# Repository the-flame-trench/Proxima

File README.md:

# Proxima
Repo for the open source Proxima AstroCamera family

## About
The Proxima AstroCamera is a general purpose CCD/CMOS imager intended for use for amateur astrophotography and citizen science/outreach.  The project aligns closely with [The Flame Trench](http://theflametrench.com)'s [Gaze](http://theflametrench.com/flagship#/gaze) robotic observatory project.  The intent is to develop configurable CCD/CMOS front-end variants and an ASCOM compatible, FPGA-based back-end compute module.  This will come in ethernet based Alpaca and USB-3 based ASCOM/native variants.

## Specifications
The following are provisional design goals of the Proxima project:
* DSLR CCD/CMOS
   * mono/bayered
   * interline/full frame
* Programmable bias voltages, to allow for the front-end to be CCD agnostic
* Tuned clocking drivers for the same reason
* Separate CMOS driver front-end variant
* Full ASCOM compliancy, for compatibility with current astrophotography/astronomy session management and capture software suites
* Active cooling, to reduce dark current noise to the minimum feasible
* USB 3 support, to prevent data downlinking causing a bottleneck within the system, and allowing for fast image frequencies
* Ethernet support in a Linux SoC/Alpaca back-end variant
* Memory buffers for fast framerate CMOS readout
* Sealed/purged cold room
   * Provisional goal which would allow for much colder CCD temperatures by absorbing or purging moisture from the enclosure
* 12-19V DC supply, to allow for AC mains + power supply or power direct from battery

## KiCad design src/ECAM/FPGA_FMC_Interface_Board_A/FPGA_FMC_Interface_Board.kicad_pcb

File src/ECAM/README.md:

# Proxima ECAM
This folder contains the electronic hardware source for the Proxima AstroCamera family.

## Project List
### Proxima_A
* ISSUE A - Proxima FEE (Front End Electronics)

## Archive
### FPGA_FMC_Interface_Board_A
* ISSUE A - MOJO v3 - FMC interconnection board for development
* Archived due to switch to Artix 7 devboard with integrated USB3 driver and DDR3 RAM

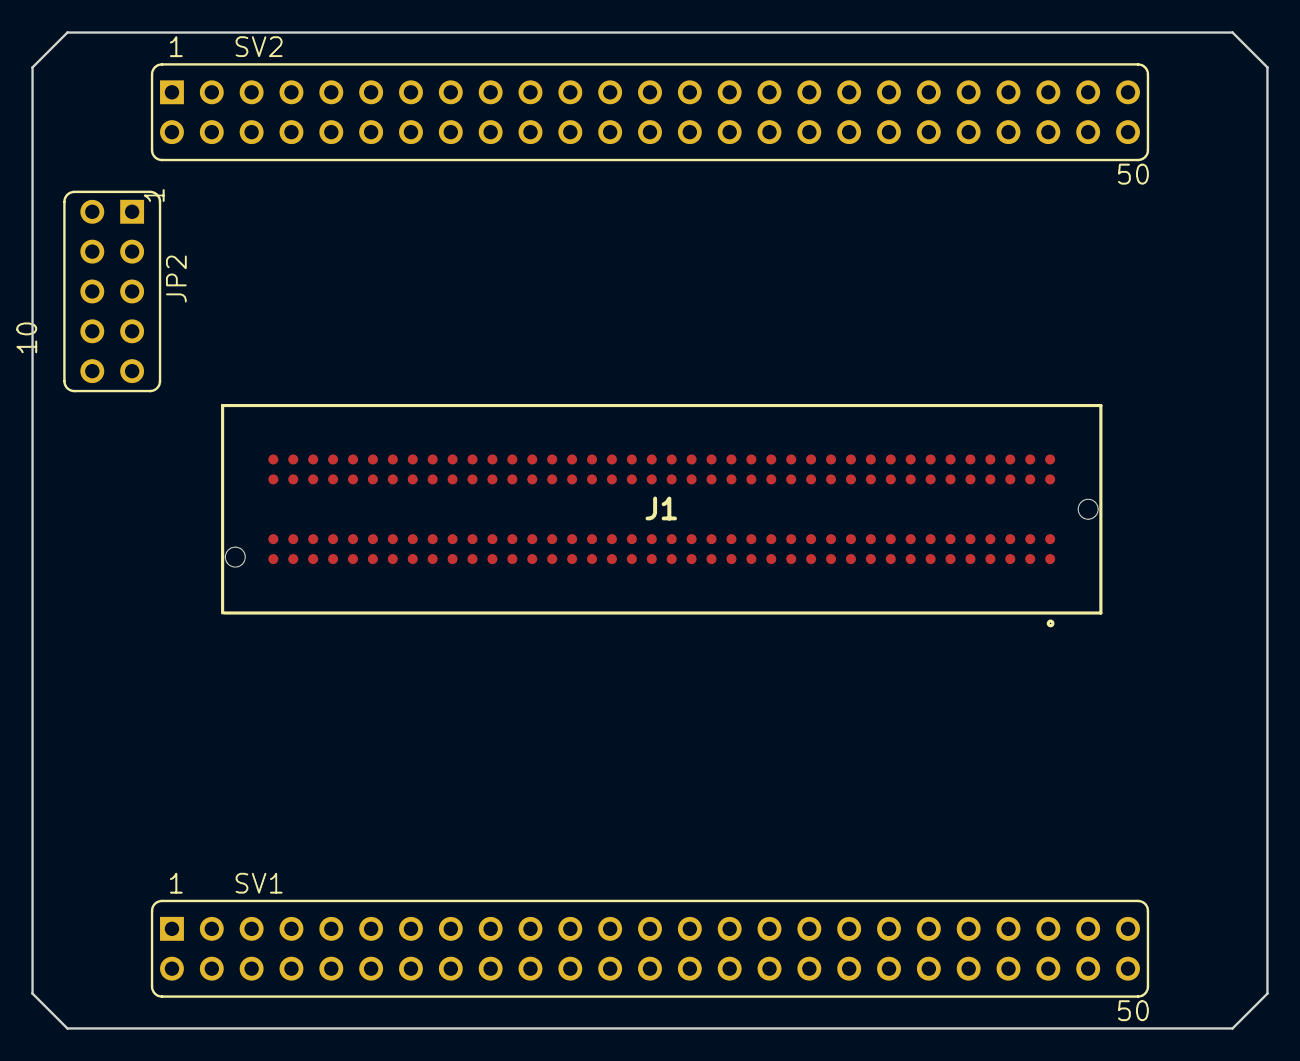
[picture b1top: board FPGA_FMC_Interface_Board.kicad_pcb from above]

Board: 4 copper layers, 78.7 x 63.5 mm, 4 parts (0 on the bottom side), 3 nets, no tracks yet.

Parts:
J1: ASP-134603-01; ASP-134604-01
JP2: FE05-2
SV1, SV2: FE25-2

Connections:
+3V3: SV1.4, SV2.4
+5V: SV1.2, SV2.2
GND: JP2.1, SV1.1, SV1.3, SV1.50, SV2.1, SV2.3

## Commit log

2019-10-13 Create LICENSE
2019-10-13 new directories
2019-10-13 git ignore added
2019-10-13 fixed git ignore
2019-10-13 removed desktop.ini
2019-10-13 added ECAM project and FPGA dir
2019-10-13 FPGA FMC interface board project added, ECAM README.md written
2019-10-13 new README written for root project
2019-10-13 readme fixes
2019-10-13 added logo graphics to ./graphics
2019-10-13 updated README with logo graphic
2019-10-13 README fix
2019-10-13 added logo with white background
2019-10-13 logo edited
2019-10-13 logo cleanup
2019-10-20 README updated with more project details and commitment to CMOS sensor architectures and ASCOM Alpaca
2019-10-20 Added software directory for driver/embedded code
2019-10-20 added mojo_v3 sch/brd for editing into FMC breakout
2019-10-20 sch cut down to connectors only
2019-10-20 added FT601 devboard datasheet
2019-10-20 added potential FMC LPC connector datasheets
2019-10-20 added mechanical dir
2019-10-20 Update issue templates
2019-10-20 Revert "Update issue templates"
2019-10-21 added FMC connector footprint, cleaned out PCB layout
2019-10-21 small board update
2019-10-21 added icon graphic
2019-10-21 working on linking header nets to FMC, dealing with some cached lib issues
2019-10-21 lib cache issues
2019-10-22 Archived FPGA_FMC_Interface_Board_A due to switching priority to a more suitable dev board
2019-10-26 first 4 sensors added
2019-10-26 all sensors added, table transposed
2019-10-26 added CAD files for frontrunner sensors
2019-10-26 FPA CAD files added
2019-10-26 added 36mm small sensor FPA stl
2019-10-26 added FPA modelling/cost stats
2019-10-26 removed lock file
2020-05-29 vhdl code which can loopback data using the ft601
